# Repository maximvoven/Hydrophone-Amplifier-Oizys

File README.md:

# Project OizysAMP

**Designer**: Maxim Vovenko

## Warning:
This was designed in High School for a club called AVBotz, this work predates my studies of EE at San Jose State University. Reuse Design at your own peral, Im not responsible for anything that happens or gurentee this works. This is only stored for historical record.

## Description:
This is the Hydrophone Amplifier Code name "Oizys". The code name reflects the absord amount of time 
figuring out how to make the amplifier and the amount of rivisions that have been trashed. This is the 
First version of the amplifer wich has been designed based on reasearch and simulations run in LTSpice
by Analog Devices. Oziys board is a three stage amplifier and filter combo witch has been tunned to
filter out signals below 20khz and above 55khz. The recommended sample rate is above 200khz. The board
Consists of three stages each one is powered by an ad8676 dual channel opamp. Dual channel opamps were
selected due to the relative little cross talk they have and there ability to process two signals at a
time. Stage one is a preamp/decoupling stage witch is required due to the use of piezoelectric 
Hydrophones. A 1 giga ohm resistor is used to stabalize and prevent saturation of the piezoelectric 
element. Stage two is an amp stage with the ability to be set to static out-put or variable output by 
selecting weather you use resistors R2A/R2B or trimpots vr1/vr2 respectively. Stage 3 is an anti-aliasing 
filter prioritizing speed over atenuation. There is a final passive stage wich offsets the signal by 1.64v 
using a high pass filter with ground replaced by 1.64v. The amp is to be tuned to function within 0-3.3v.
Resources used to build this design are included and so is a BOM.

While the material distrubuted with the mit license I can not and do not take credit for any work done except
for the following files: HydrophoneAmpliferCircuit.sch, HydrophoneAmpliferCircuit.brd, README.md, BOM.ods,AmpV0.asc
the files listed above are as a result of my work and are as a result covered under MIT License.

## Software Used: 
Eagle, LTSPICEXVII

## Known Issues:
-Design is suboptimal, the stages for amplification and signal conditioning should be reversed to prevent clipping
-Power Supply instantly fails under _any_ transient voltage spikes.
-Improper Crimping may result in damage to power supply due to no reverse polarity protection being present and software engineers not being able to decode wire coloring.
-The reference voltage is coupled to the signal producing artifacts in the signal, this needs to be decoupled.
-Gain calculations may be off by factor of 10, recalculation required (Symptoms: Signal observed to be in 10mv range instead of 1v).

## Revision History:
V1.2
-Updated License
-OpenSourced with MIT License
-Updated Silkscreens to reflect new state of the project.

V1.1
-Miscillaneous changes
-Moved around silkscreen for ease of assembly
-DRC Check Cleared
-Added OshaPark DRC

V1.0
-Finalized Schematic
-Created and finalized board layout and traces.
-Created Silk Screens.

V0.3
-Finalized Schematic
-Updated Library With Necessary Componets
-Organized BRD slightly before building final board

V0.2
-Semi-final design
-LTspiceXVII Simulation Files Added
-1.6V Rail Created 
-1.6v Filtering added using 1uf
-Identified resistor to replace with pot
TODO:
-Calculate Amplifier Circuit to add calibration ability
-Add C Filtering to 24v rail
-Add C Filter 12v
-Add C Filter -12v 

V0.1.1
-Renamed to  "Project OizysAMP"
-Updated Capcitors In Filtering circuit to accuratly reflect components being installed
-Lost hope in humanity
-Wished that power supply filtering was as easy as it is to say power supply filtering

V0.1
Initial Incomplete design
-Missing Power supply filtering
-missing connectors
-Missing Board Design
-missing design constraints
-Completed amplyfiying circuit
-Missing trim pot for tuning amp circuit
-Testpoints were added to faciilitate diagnostics.

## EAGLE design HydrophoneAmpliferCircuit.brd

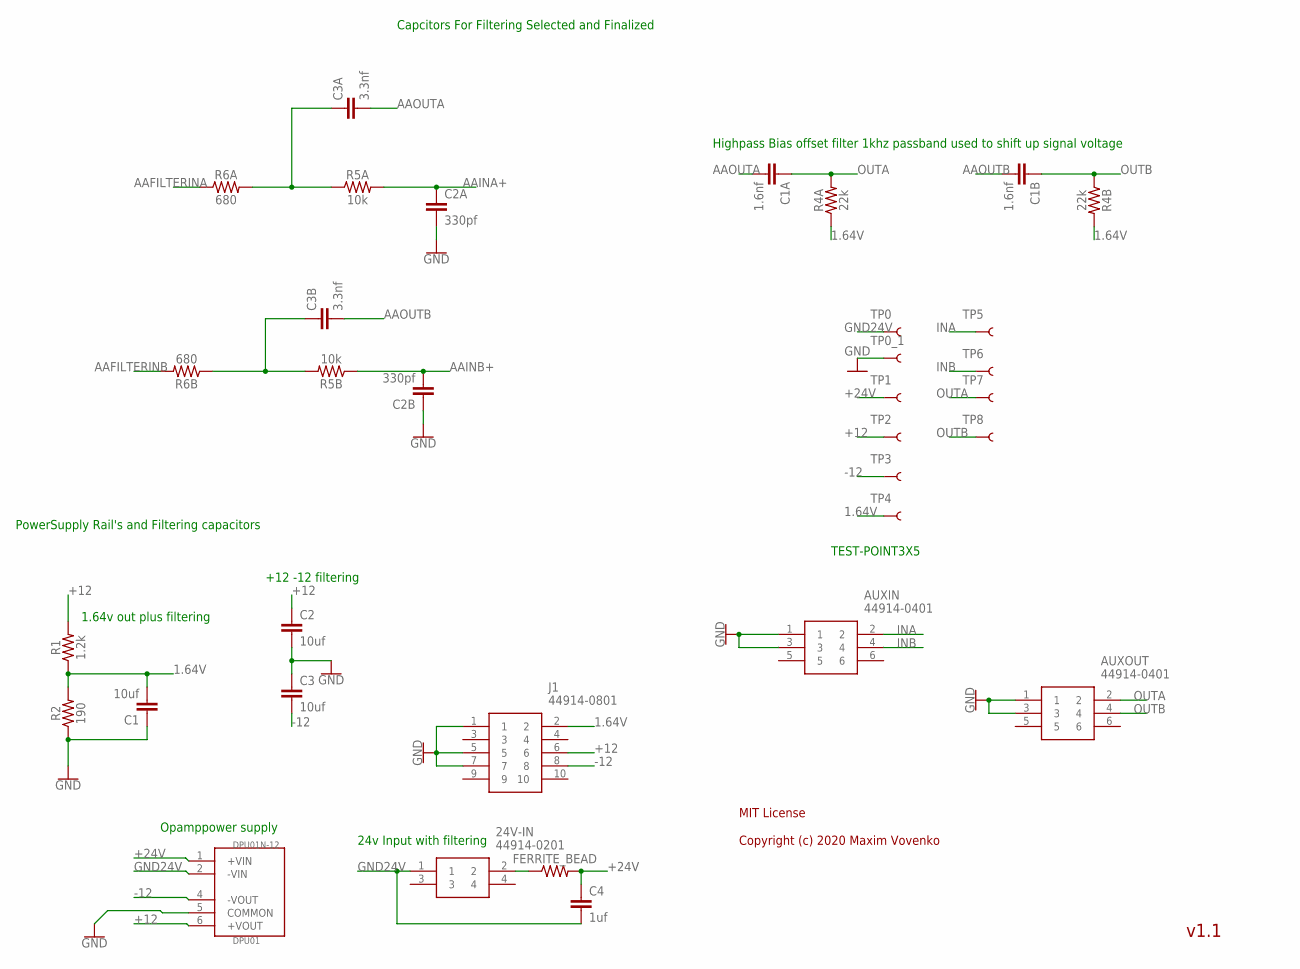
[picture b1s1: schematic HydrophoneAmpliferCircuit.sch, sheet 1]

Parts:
24V-IN: 44914-0201; 449140201
AUXIN: 44914-0401; 449140401
AUXOUT: 44914-0401; 449140401
C1, C2, C3: 10uf; C5B7.2
C1A, C1B: 1.6nf; C2.5-5
C2A, C2B: 330pf; C5B3.5
C3A, C3B: 3.3nf; C5B3
C4: 1uf; C5B7.2
DPU01N-12: DPU01
FERRITE_BEAD: AXIAL-0.3
J1: 44914-0801; 449140801
R1: 1.2k; AXIAL-0.3
R2: 190; AXIAL-0.3
R4A, R4B: 22k; AXIAL-0.3
R5A, R5B: 10k; AXIAL-0.3
R6A, R6B: 680; AXIAL-0.3
TP0, TP0_1, TP1, TP2, TP3, TP4, TP5, TP6, TP7, TP8: TEST-POINT3X5; PAD.03X.05

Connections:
1.64V: C1.2, J1.2, R1.P$1 (1), R2.P$2 (2), R4A.P$1 (1), R4B.P$2 (2), TP4.P$1
+12: C2.1, DPU01N-12.6 (+VOUT), J1.6, R1.P$2 (2), TP2.P$1; also elsewhere on the board
+24V: C4.1, DPU01N-12.1 (+VIN), FERRITE_BEAD.P$2 (2), TP1.P$1
-12: C3.2, DPU01N-12.4 (-VOUT), J1.8, TP3.P$1; also elsewhere on the board
AAFILTERINA: R6A.P$1 (1); also elsewhere on the board
AAFILTERINB: R6B.P$2 (2); also elsewhere on the board
AAINA+: C2A.1, R5A.P$2 (2); also elsewhere on the board
AAINB+: C2B.2, R5B.P$1 (1); also elsewhere on the board
AAOUTA: C1A.2, C3A.2; also elsewhere on the board
AAOUTB: C1B.2, C3B.2; also elsewhere on the board
GND: AUXIN.1, AUXIN.3, AUXOUT.1, AUXOUT.3, C1.1, C2.2, C2A.2, C2B.1, C3.1, DPU01N-12.5 (COMMON), J1.1, J1.5, J1.7, R2.P$1 (1), TP0_1.P$1; also elsewhere on the board
GND24V: 24V-IN.1, C4.2, DPU01N-12.2 (-VIN), TP0.P$1
INA: AUXIN.2, TP5.P$1; also elsewhere on the board
INB: AUXIN.4, TP6.P$1; also elsewhere on the board
unnamed: C3B.1, R5B.P$2 (2), R6B.P$1 (1)
unnamed: 24V-IN.2, FERRITE_BEAD.P$1 (1)
unnamed: C3A.1, R5A.P$1 (1), R6A.P$2 (2)
OUTA: AUXOUT.2, C1A.1, R4A.P$2 (2), TP7.P$1; also elsewhere on the board
OUTB: AUXOUT.4, C1B.1, R4B.P$1 (1), TP8.P$1; also elsewhere on the board

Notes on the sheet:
Capcitors For Filtering Selected and Finalized
Highpass Bias offset filter 1khz passband used to shift up signal voltage
Opamppower supply
PowerSupply Rail's and Filtering capacitors
TEST-POINT3X5
24v Input with filtering
+12 -12 filtering
1.64v out plus filtering
v1.1
MIT License Copyright (c) 2020 Maxim Vovenko

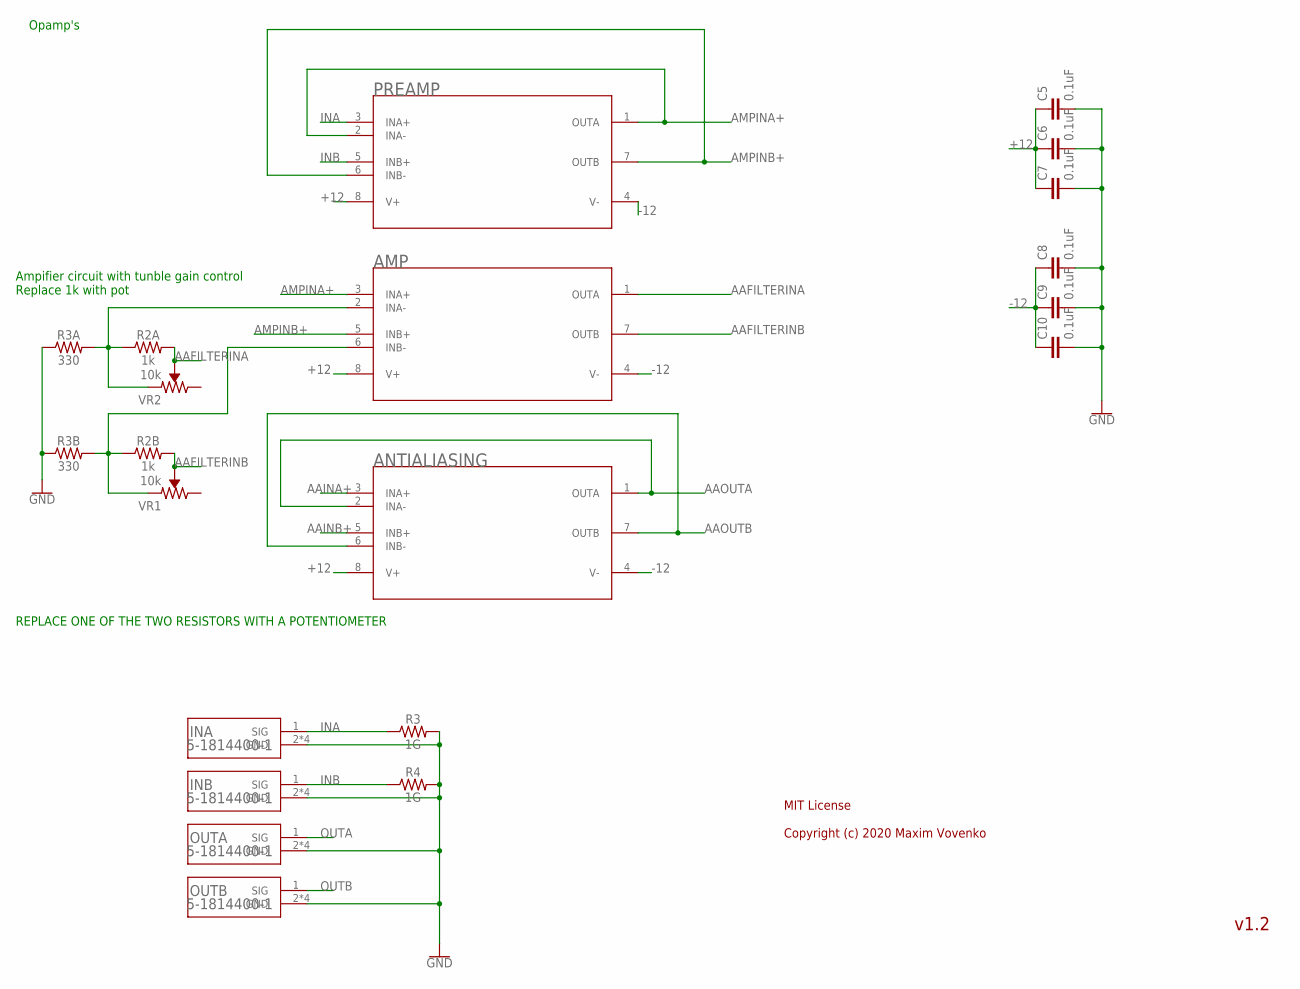
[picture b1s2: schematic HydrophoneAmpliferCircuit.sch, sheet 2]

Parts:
AMP: AD8676ARZR_8-M; R_8-M
ANTIALIASING: AD8676ARZR_8-M; R_8-M
C5, C6, C7, C8, C9, C10: 0.1uF; 0603
INA: 5-1814400-1
INB: 5-1814400-1
OUTA: 5-1814400-1
OUTB: 5-1814400-1
PREAMP: AD8676ARZR_8-M; R_8-M
R2A, R2B: 1k; AXIAL-0.3
R3, R4: 1G; AXIAL-0.3
R3A, R3B: 330; AXIAL-0.3
VR1, VR2: 10k; TRIMPOT-PTH-3386U

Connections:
+12: AMP.8 (V+), ANTIALIASING.8 (V+), C5.1, C6.1, C7.1, PREAMP.8 (V+); also elsewhere on the board
-12: AMP.4 (V-), ANTIALIASING.4 (V-), C8.1, C9.1, C10.1, PREAMP.4 (V-); also elsewhere on the board
AAFILTERINA: AMP.1 (OUTA), R2A.P$2 (2), VR2.2 (WIPER); also elsewhere on the board
AAFILTERINB: AMP.7 (OUTB), R2B.P$2 (2), VR1.2 (WIPER); also elsewhere on the board
AAINA+: ANTIALIASING.3 (INA+); also elsewhere on the board
AAINB+: ANTIALIASING.5 (INB+); also elsewhere on the board
AAOUTA: ANTIALIASING.1 (OUTA), ANTIALIASING.2 (INA-); also elsewhere on the board
AAOUTB: ANTIALIASING.6 (INB-), ANTIALIASING.7 (OUTB); also elsewhere on the board
AMPINA+: AMP.3 (INA+), PREAMP.1 (OUTA), PREAMP.2 (INA-)
AMPINB+: AMP.5 (INB+), PREAMP.6 (INB-), PREAMP.7 (OUTB)
GND: C5.2, C6.2, C7.2, C8.2, C9.2, C10.2, INA.2 (GND), INA.3 (GND), INA.4 (GND), INA.5 (GND), INB.2 (GND), INB.3 (GND), INB.4 (GND), INB.5 (GND), OUTA.2 (GND), OUTA.3 (GND), OUTA.4 (GND), OUTA.5 (GND), OUTB.2 (GND), OUTB.3 (GND), OUTB.4 (GND), OUTB.5 (GND), R3.P$2 (2), R3A.P$1 (1), R3B.P$1 (1), R4.P$2 (2); also elsewhere on the board
INA: INA.1 (SIG), PREAMP.3 (INA+), R3.P$1 (1); also elsewhere on the board
INB: INB.1 (SIG), PREAMP.5 (INB+), R4.P$1 (1); also elsewhere on the board
unnamed: AMP.2 (INA-), R2A.P$1 (1), R3A.P$2 (2), VR2.1 (CCW)
unnamed: AMP.6 (INB-), R2B.P$1 (1), R3B.P$2 (2), VR1.1 (CCW)
OUTA: OUTA.1 (SIG); also elsewhere on the board
OUTB: OUTB.1 (SIG); also elsewhere on the board

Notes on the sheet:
Ampifier circuit with tunble gain control Replace 1k with pot
Opamp's
REPLACE ONE OF THE TWO RESISTORS WITH A POTENTIOMETER
v1.2
MIT License Copyright (c) 2020 Maxim Vovenko

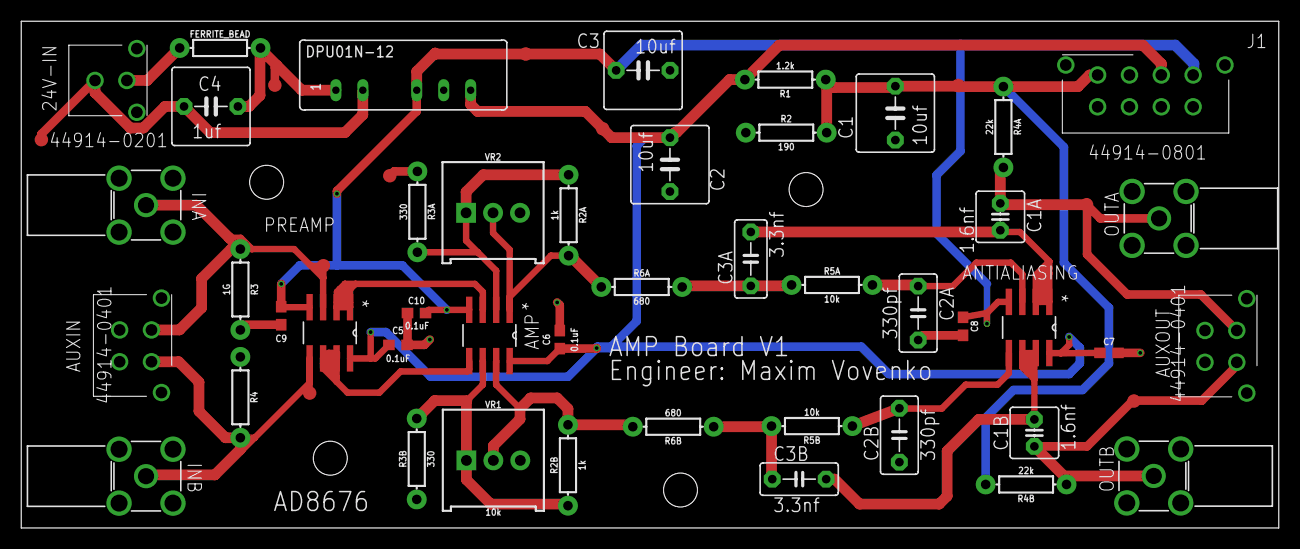
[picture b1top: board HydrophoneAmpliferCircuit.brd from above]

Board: 2 copper layers, 118.5 x 47.8 mm, 55 parts (0 on the bottom side), 23 nets.

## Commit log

2020-02-10 Init

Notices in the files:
parts and their libraries:
SparkFun-Resistors: Licensing: Creative Commons ShareAlike 4.0 International - https://creativecommons.org/licenses/by-sa/4.0
